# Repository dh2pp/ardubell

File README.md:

# ardubell

This project is for people who live in a flat and don't want to carry along their keys when they just leave home for shopping etc. You can simply use the Door bell button and type a pattern (compare Morse Code) and - provided that you have a remote unlock button from inside your flat - get the door unlocked automatically.

Code is working, but not nice :/ Hope to find some time to make it better (interrupt waking up from sleep, ...)

**Disclaimer**: Of course, this is not very secure but may be secure enough for the public front door to the stair case. I thought about a challenge response, but the only channel to transmit the challenge to the person at the front door is unlocking the door ^^ Feel free to share your thoughts/improvements in an issue.

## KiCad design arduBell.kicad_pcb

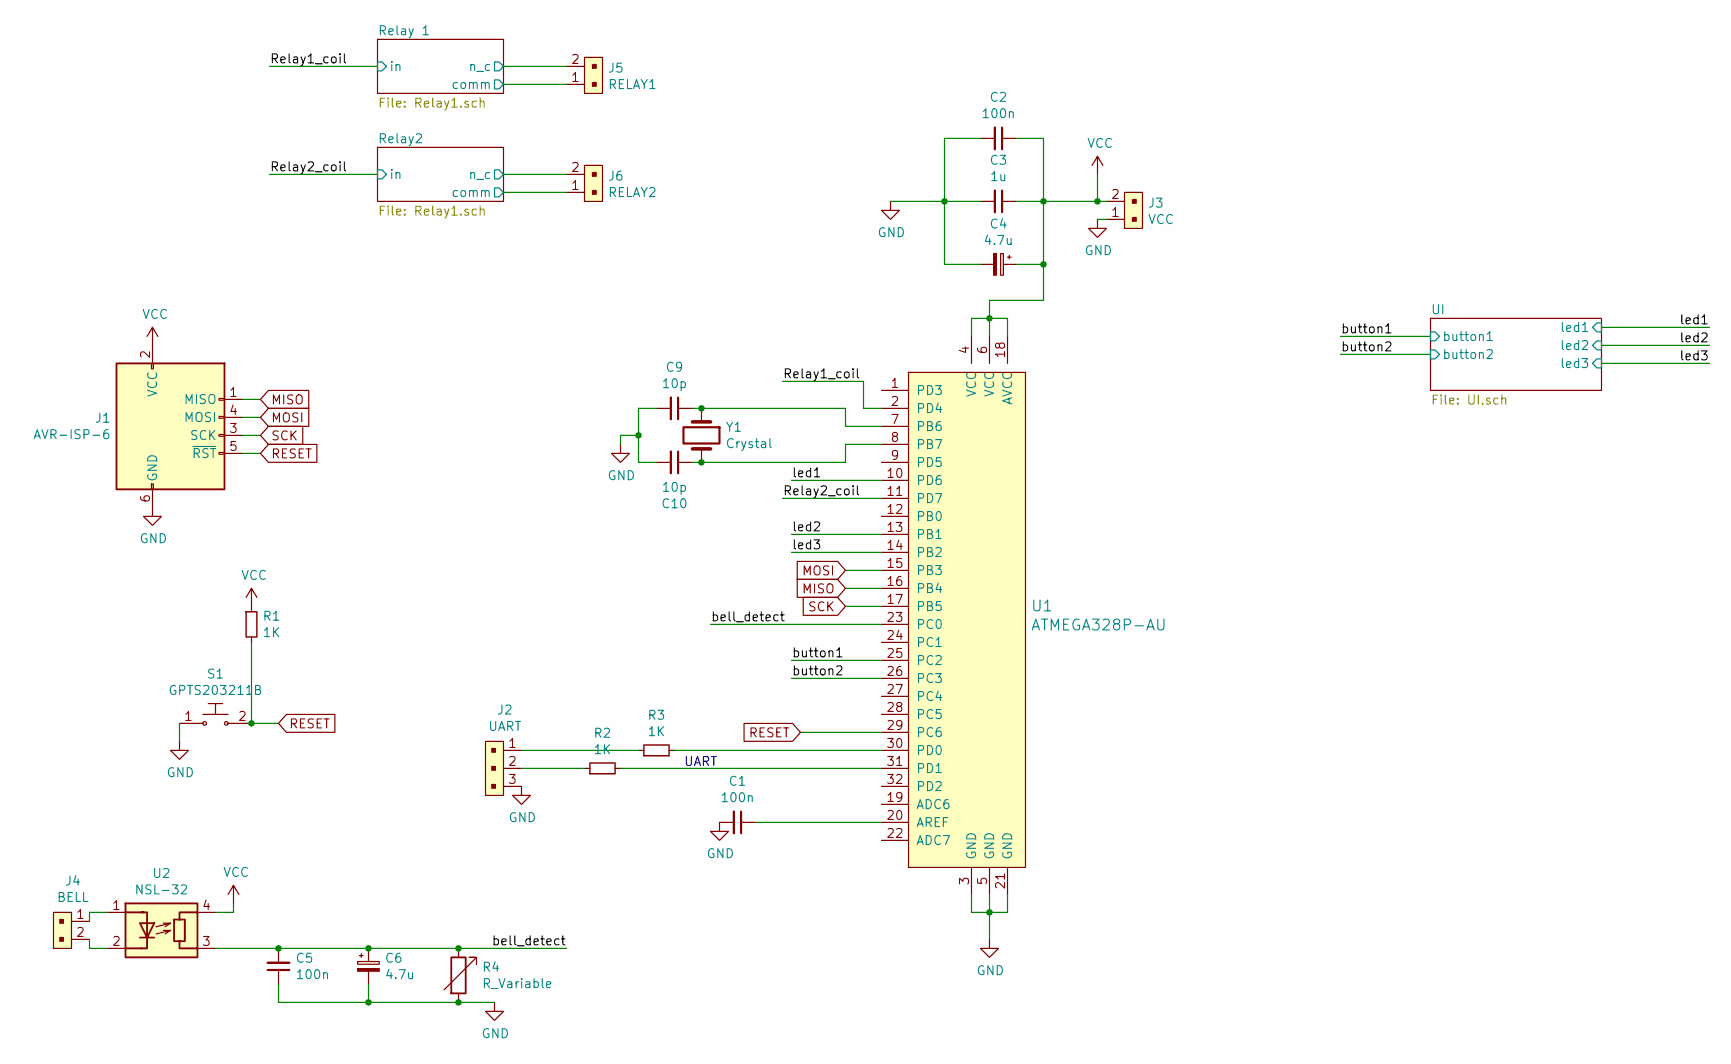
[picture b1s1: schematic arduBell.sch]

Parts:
C1, C2, C5: 100n; C_0603_1608Metric
C3: 1u; C_0603_1608Metric
C4, C6: 4.7u; C_1206_3216Metric
C9, C10: 10p; C_0603_1608Metric
J1: AVR-ISP-6; PinHeader_2x03_P2.54mm_Horizontal
J2: UART; PinHeader_1x3_P2.54_Drill1.1mm; MPN 640456-3; Digi-Key_PN A19470-ND
J3: VCC; PinHeader_1x2_P2.54mm_Drill1.02mm; MPN 22-23-2021; Digi-Key_PN WM4200-ND
J4: BELL; PinHeader_1x2_P2.54mm_Drill1.02mm; MPN 22-23-2021; Digi-Key_PN WM4200-ND
J5: RELAY1; PinHeader_1x2_P2.54mm_Drill1.02mm; MPN 22-23-2021; Digi-Key_PN WM4200-ND
J6: RELAY2; PinHeader_1x2_P2.54mm_Drill1.02mm; MPN 22-23-2021; Digi-Key_PN WM4200-ND
R1, R2, R3: 1K; R_0603_1608Metric
R4: R_Variable; Potentiometer_Bourns_3386P_Vertical
S1: GPTS203211B; SW_PUSH_6mm; MPN GPTS203211B; Digi-Key_PN CW181-ND
U1: ATMEGA328P-AU; TQFP-32_7x7mm; MPN ATMEGA328P-AU; Digi-Key_PN ATMEGA328P-AU-ND
U2: NSL-32; DIP-4_W8.89mm_SMDSocket_LongPads
Y1: Crystal

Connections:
/Relay1_coil: U1.2 (PD4); also elsewhere on the board
/Relay2/comm: J6.1; also elsewhere on the board
/Relay2/n_c: J6.2; also elsewhere on the board
/Relay2_coil: U1.11 (PD7); also elsewhere on the board
/Relay 1/comm: J5.1; also elsewhere on the board
/Relay 1/n_c: J5.2; also elsewhere on the board
/bell_detect: C5.2, C6.1, R4.1, U1.23 (PC0), U2.3 (R)
/button1: U1.25 (PC2); also elsewhere on the board
/button2: U1.26 (PC3); also elsewhere on the board
/led1: U1.10 (PD6); also elsewhere on the board
/led2: U1.13 (PB1); also elsewhere on the board
/led3: U1.14 (PB2); also elsewhere on the board
GND: C1.2, C2.2, C3.2, C4.2, C5.1, C6.2, C9.2, C10.2, J1.6 (GND), J2.3, J3.1, R4.2, S1.1, U1.3 (GND), U1.5 (GND), U1.21 (GND); also elsewhere on the board
MISO: J1.1 (MISO), U1.16 (PB4)
MOSI: J1.4 (MOSI), U1.15 (PB3)
unnamed: C1.1, U1.20 (AREF)
unnamed: C9.1, U1.7 (PB6), Y1.1
unnamed: C10.1, U1.8 (PB7), Y1.2
unnamed: J2.1, R3.1
unnamed: J2.2, R2.1
unnamed: J4.1, U2.1 (A)
unnamed: J4.2, U2.2 (K)
unnamed: R2.2, U1.31 (PD1)
unnamed: R3.2, U1.30 (PD0)
RESET: J1.5 (~RST), R1.2, S1.2, U1.29 (PC6)
SCK: J1.3 (SCK), U1.17 (PB5)
VCC: C2.1, C3.1, C4.1, J1.2 (VCC), J3.2, R1.1, U1.4 (VCC), U1.6 (VCC), U1.18 (AVCC), U2.4 (R); also elsewhere on the board

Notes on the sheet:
UART

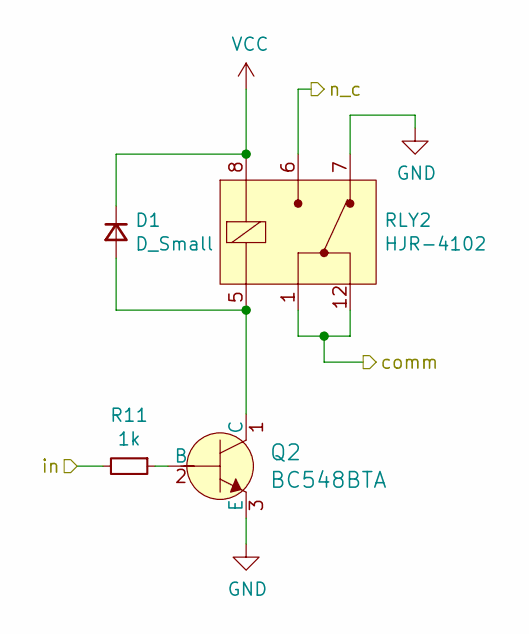
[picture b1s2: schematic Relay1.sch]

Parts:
D2: D_Small; D_DO-34_SOD68_P7.62mm_Horizontal
Q1: BC548BTA; TO-92L_Inline; MPN BC548BTA; Digi-Key_PN BC548BTACT-ND
R10: 1k; R_0603_1608Metric
RLY1: HJR-4102; Relay_SPDT_HJR-4102

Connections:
/Relay1_coil: R10.2; also elsewhere on the board
/Relay 1/comm: RLY1.1 (COM), RLY1.12 (COM); also elsewhere on the board
/Relay 1/n_c: RLY1.6 (NO); also elsewhere on the board
GND: Q1.3 (E), RLY1.7 (NC); also elsewhere on the board
unnamed: D2.2 (A), Q1.1 (C), RLY1.5 (COIL)
unnamed: Q1.2 (B), R10.1
VCC: D2.1 (K), RLY1.8 (COIL); also elsewhere on the board

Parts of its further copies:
D1: D_Small; D_DO-34_SOD68_P7.62mm_Horizontal
Q2: BC548BTA; TO-92L_Inline; MPN BC548BTA; Digi-Key_PN BC548BTACT-ND
R11: 1k; R_0603_1608Metric
RLY2: HJR-4102; Relay_SPDT_HJR-4102

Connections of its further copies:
/Relay2/comm: RLY2.1 (COM), RLY2.12 (COM); also elsewhere on the board
/Relay2/n_c: RLY2.6 (NO); also elsewhere on the board
/Relay2_coil: R11.2; also elsewhere on the board
GND: Q2.3 (E), RLY2.7 (NC); also elsewhere on the board
unnamed: D1.2 (A), Q2.1 (C), RLY2.5 (COIL)
unnamed: Q2.2 (B), R11.1
VCC: D1.1 (K), RLY2.8 (COIL); also elsewhere on the board

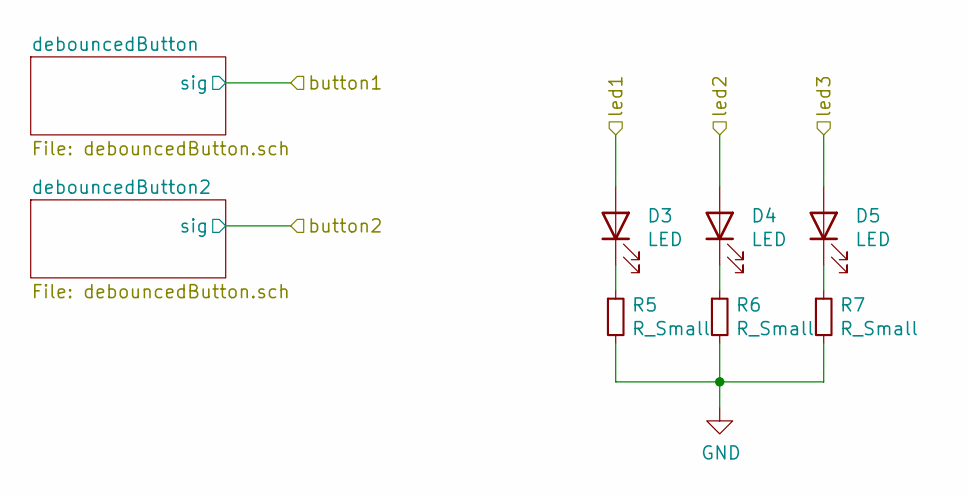
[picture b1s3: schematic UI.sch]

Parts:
D3, D4, D5: LED; LED_D5.0mm
R5, R6, R7: R_Small; R_0603_1608Metric

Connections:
/led1: D3.2 (A); also elsewhere on the board
/led2: D4.2 (A); also elsewhere on the board
/led3: D5.2 (A); also elsewhere on the board
GND: R5.2, R6.2, R7.2; also elsewhere on the board
unnamed: D3.1 (K), R5.1
unnamed: D4.1 (K), R6.1
unnamed: D5.1 (K), R7.1

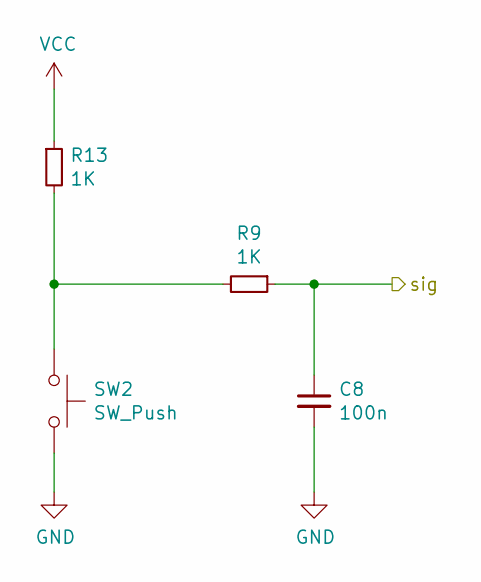
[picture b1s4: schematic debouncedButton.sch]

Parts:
C7: 100n; C_0603_1608Metric
R8, R12: 1K; R_0603_1608Metric
SW1: SW_Push; SW_PUSH_6mm

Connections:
/button1: C7.1, R8.1; also elsewhere on the board
GND: C7.2, SW1.2; also elsewhere on the board
unnamed: R8.2, R12.2, SW1.1
VCC: R12.1; also elsewhere on the board

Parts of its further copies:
C8: 100n; C_0603_1608Metric
R9, R13: 1K; R_0603_1608Metric
SW2: SW_Push; SW_PUSH_6mm

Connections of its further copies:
/button2: C8.1, R9.1; also elsewhere on the board
GND: C8.2, SW2.2; also elsewhere on the board
unnamed: R9.2, R13.2, SW2.1
VCC: R13.1; also elsewhere on the board

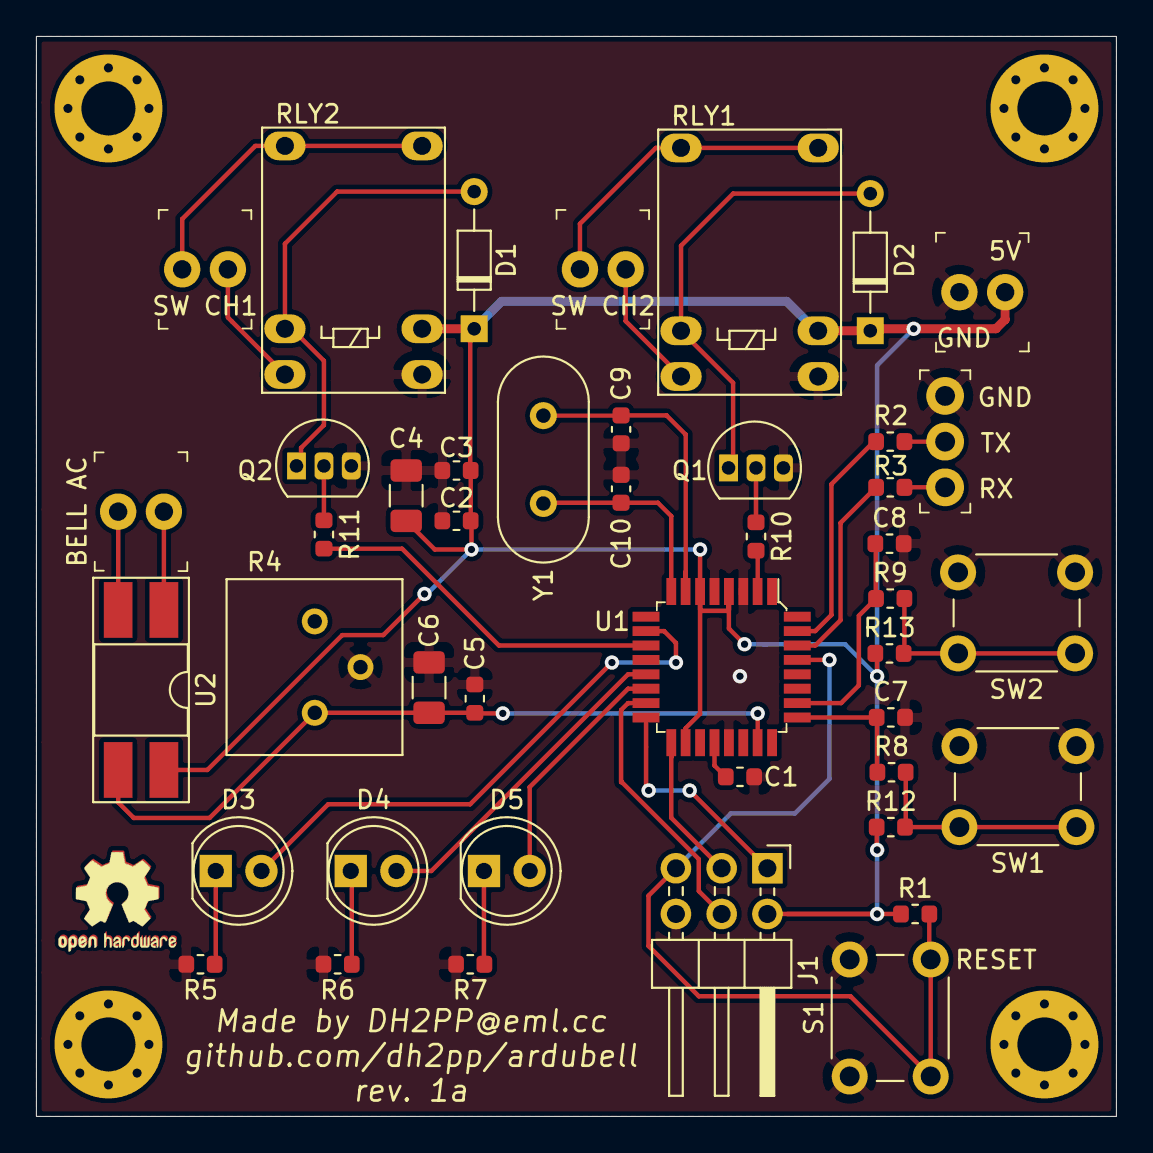
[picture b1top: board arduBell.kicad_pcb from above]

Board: 2 copper layers, 60.0 x 60.0 mm, 48 parts (0 on the bottom side), 36 nets.

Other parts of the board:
 : MountingHole_3mm_Pad_Via
 #2,  #3,  #4: MountingHole_3mm_Pad_Via

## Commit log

2021-03-10 1st check
2021-05-10 rev 1a, XO fixed, more labels and rearranging
2021-08-18 rev 1a: optocoupler works, quarz works
2023-04-03 inital SW commit
2023-04-03 move into folder so IDE is happy
2023-04-03 cleaned code
2023-04-03 cleaned code, again
